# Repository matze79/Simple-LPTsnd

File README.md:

Covox Speech Thing Compatible Sound Adapter for LPT Port

http://www.retroianer.de

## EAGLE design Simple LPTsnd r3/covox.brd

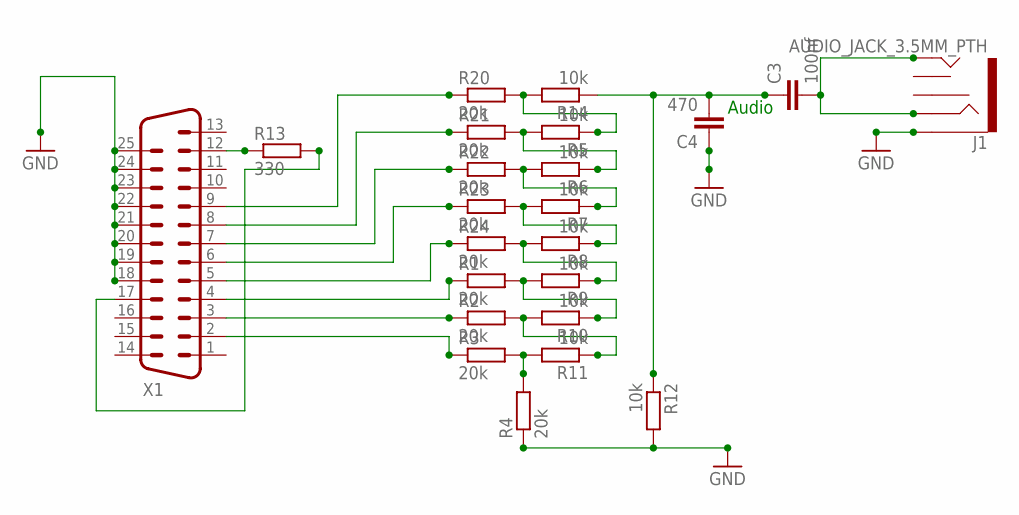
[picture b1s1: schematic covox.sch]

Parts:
C3: 100nf; C0805K
C4: 470; C0805K
J1: AUDIO_JACK_3.5MM_PTH; AUDIO-JACK
R1, R2, R3, R4, R20, R21, R22, R23, R24: 20k; M0805
R5, R6, R7, R8, R9, R10, R11, R12, R14: 10k; M0805
R13: 330; M0805
X1: M25HP

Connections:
D0: R3.1, X1.2
D1: R2.1, X1.3
D2: R1.1, X1.4
D3: R24.1, X1.5
D4: R23.1, X1.6
D5: R22.1, X1.7
D6: R21.1, X1.8
D7: R20.1, X1.9
GND: C4.1, J1.SLEEVE, R4.1, R12.2, X1.18, X1.19, X1.20, X1.21, X1.22, X1.23, X1.24, X1.25
unnamed: R3.2, R4.2, R11.2
unnamed: R2.2, R10.2, R11.1
unnamed: R1.2, R9.2, R10.1
unnamed: R7.2, R8.1, R23.2
unnamed: C3.2, J1.RING, J1.TIP
unnamed: R6.2, R7.1, R22.2
unnamed: R5.2, R6.1, R21.2
unnamed: R5.1, R14.2, R20.2
unnamed: C3.1, C4.2, R12.1, R14.1
unnamed: R8.2, R9.1, R24.2
unnamed: R13.2, X1.17
unnamed: R13.1, X1.12

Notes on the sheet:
Audio

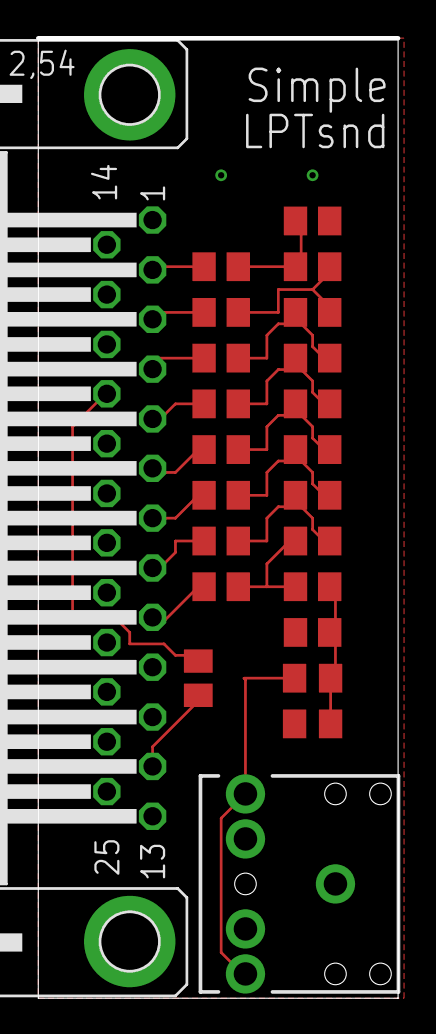
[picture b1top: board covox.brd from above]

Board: 2 copper layers, 20.0 x 53.2 mm, 23 parts (0 on the bottom side), 21 nets.

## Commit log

2025-11-23 Add project description to README
2025-11-23 Create LICENSE
2025-11-23 Add link to Covox Speech Thing website
    Add website link for Covox Speech Thing.

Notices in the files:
parts and their libraries:
SparkFun-Connectors: Licensing: Creative Commons ShareAlike 4.0 International - https://creativecommons.org/licenses/by-sa/4.0
